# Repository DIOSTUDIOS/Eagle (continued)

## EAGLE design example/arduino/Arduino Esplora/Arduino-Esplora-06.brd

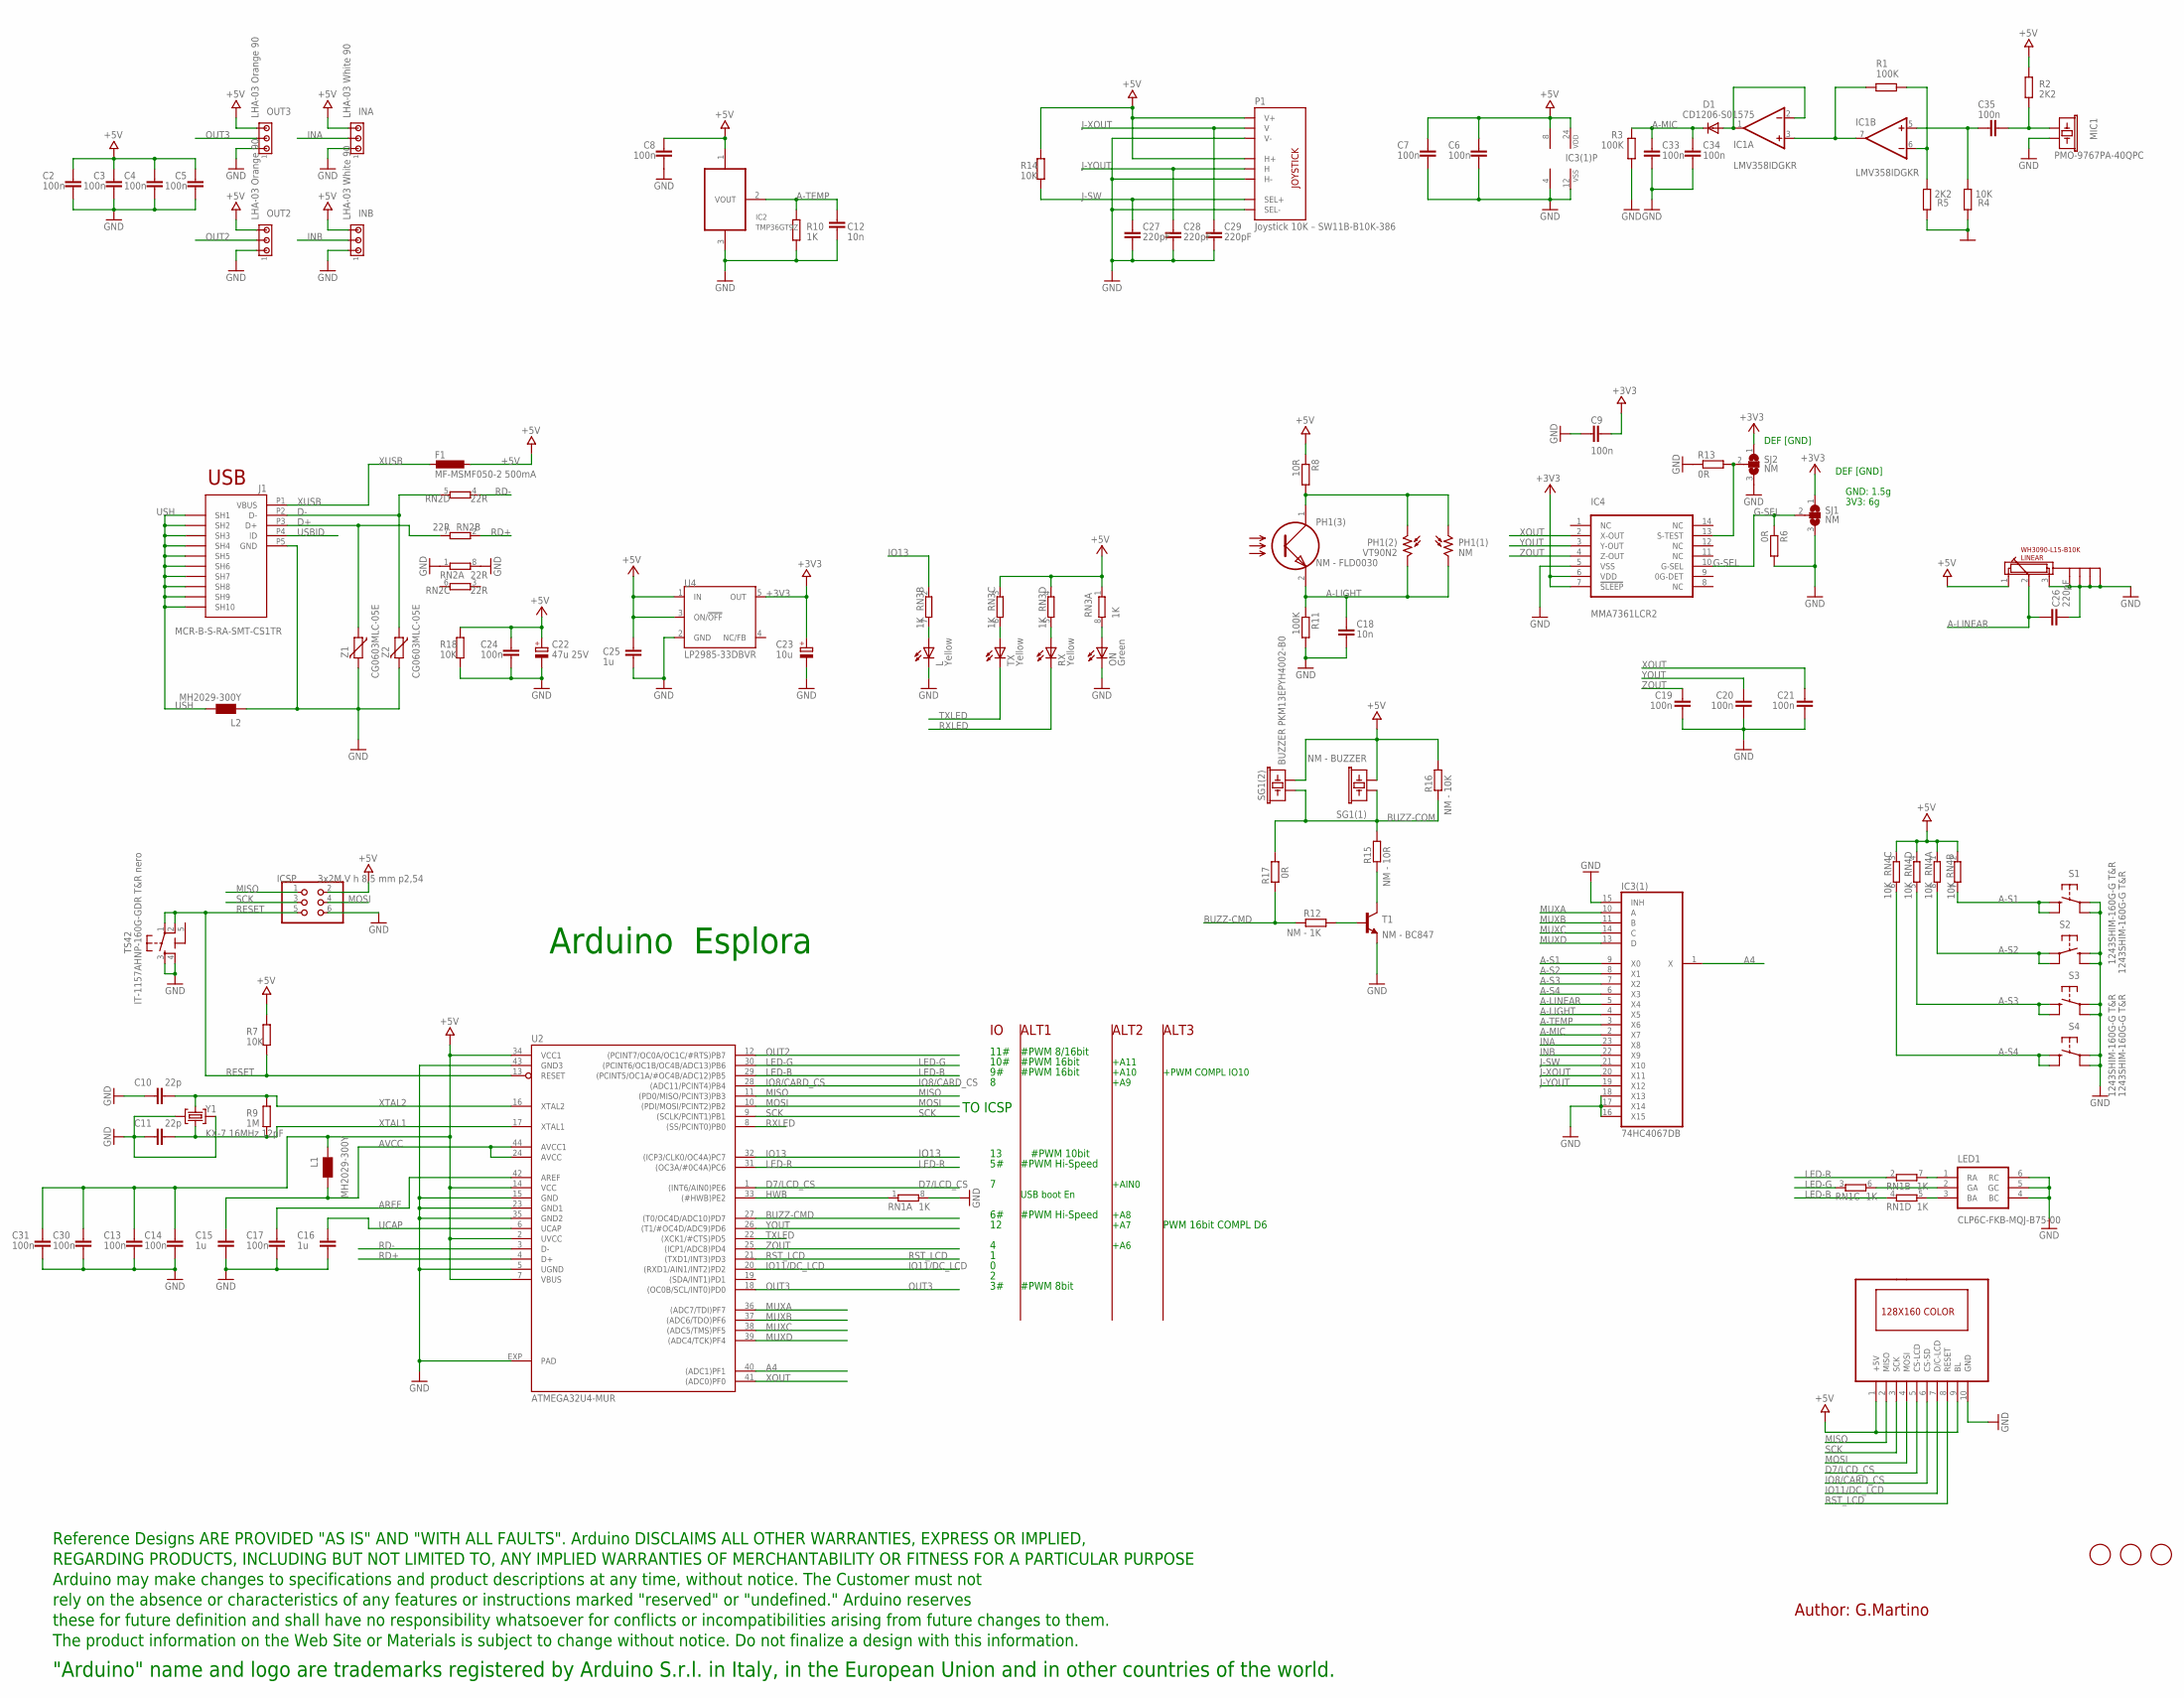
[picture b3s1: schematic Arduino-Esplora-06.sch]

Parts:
C2, C3, C4, C5, C6, C7, C8, C9, C13, C14, C17, C19, C20, C21, C24, C30, C31, C33, C34, C35: 100n; C0603-ROUND
C10, C11: 22p; C0603-ROUND
C12, C18: 10n; C0603-ROUND
C15, C16, C25: 1u; C0603-ROUND
C22: 47u 25V; PANASONIC_D
C23: 10u; SMC_B
C26, C27, C28, C29: 220pF; C0603-ROUND
D1: CD1206-S01575; MINIMELF
F1: MF-MSMF050-2 500mA; L1812
FID1, FID2, FID3: FIDUCIALMOUNT; FIDUCIA-MOUNT
IC1: LMV358IDGKR; MSOP08
IC2: TMP36GT9Z; TO92
IC3(1): 74HC4067DB; SSOP24(0.65)
IC4: MMA7361LCR2; LGA-14_3X5/0.8
ICSP: 3x2M V h 8,5 mm p2,54; 2X03
INA: LHA-03 White 90; 10X03MTA
INB: LHA-03 White 90; 10X03MTA
J1: MCR-B-S-RA-SMT-CS1TR; CON2_USB_MICRO_B_AT
L: Yellow; CHIPLED_0805
L1, L2: MH2029-300Y; 0805
LCD1: LCD1; 1.8'_LCD-LCD-TFT(128X160)
LED1: CLP6C-FKB-MQJ-B75-00; RGB-LED
LINEAR: WH3090-L15-B10K; RA3021-202
MIC1: PMO-9767PA-40QPC; MIC-9.7MM
ON: Green; CHIPLED_0805
OUT2, OUT3: LHA-03 Orange 90; 10X03MTA
P1: Joystick 10K – SW11B-B10K-386; ALP_JOYSTICK
PH1(1): NM; T0-46-A10XX
PH1(2): VT90N2; TO-8_B10
PH1(3): NM - FLD0030; FLD00030
R1, R3, R11: 100K; R0603-ROUND
R2, R5: 2K2; R0603-ROUND
R4, R7, R14, R18: 10K; R0603-ROUND
R6, R13, R17: 0R; R0603-ROUND
R8: 10R; R0603-ROUND
R9: 1M; R0603-ROUND
R10: 1K; R0603-ROUND
R12: NM - 1K; R0603-ROUND
R15: NM - 10R; R0603-ROUND
R16: NM - 10K; R0603-ROUND
RN1, RN3: 1K; CAY16
RN2: 22R; CAY16
RN4: 10K; CAY16
RX: Yellow; CHIPLED_0805
S1, S2, S3, S4: 1243SHIM-160G-G T&R; TACTILE-SMD-12MM
SG1(1): NM - BUZZER; BUZZER-12MM-NS-P5MM
SG1(2): BUZZER PKM13EPYH4002-B0; BUZZER-12MM-NS-KIT
SJ1, SJ2: NM; SJ_2
T1: NM - BC847; SOT23
TS42: IT-1157AHNP-160G-GDR T&R nero; TS42
TX: Yellow; CHIPLED_0805
U2: ATMEGA32U4-MUR; QFN44ML7X7
U4: LP2985-33DBVR; SOT23-DBV
U$19: DISCLAIMER
Y1: KX-7 16MHz 12pF; CRYSTAL-3.2-2.5
Z1, Z2: CG0603MLC-05E; CT/CN0603

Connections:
5-GND: TS42.5 (5-GND)
+3V3: C9.2, C23.+, IC4.6 (VDD), IC4.7 (!SLEEP), SJ1.1, SJ2.1, U4.5 (OUT)
+5V: C2.2, C3.2, C4.2, C5.2, C6.2, C7.2, C8.2, C13.1, C14.1, C22.+, C24.2, C25.2, C30.1, C31.1, F1.1, IC1.8 (V+), IC2.1 (+VS), IC3(1).24 (VDD), ICSP.2, INA.3, INB.3, L1.1, LCD1.1 (+5V), LCD1.9 (BL), LINEAR.1, OUT2.3, OUT3.3, P1.H1 (H+), P1.V1 (V+), R2.1, R7.1, R8.1, R14.1, R16.1, R18.1, RN3.1, RN3.3 (1), RN3.4 (1), RN4.1, RN4.2 (1), RN4.3 (1), RN4.4 (1), SG1(1).- (2), SG1(2).- (2), U2.2 (UVCC), U2.7 (VBUS), U2.14 (VCC), U2.34 (VCC1), U4.1 (IN), U4.3 (ON/!OFF)
A4: IC3(1).1 (X), U2.40 ((ADC1)PF1)
A-LIGHT: C18.2, IC3(1).4 (X5), PH1(1).2, PH1(2).2, PH1(3).2, R11.1
A-LINEAR: C26.2, IC3(1).5 (X4), LINEAR.2
A-MIC: C33.2, C34.2, D1.C, IC3(1).2 (X7), R3.1
A-S1: IC3(1).9 (X0), RN4.7 (2), S1.P$3 (3), S1.P$4 (4)
A-S2: IC3(1).8 (X1), RN4.8 (2), S2.P$1 (1), S2.P$2 (2)
A-S3: IC3(1).7 (X2), RN4.5 (2), S3.P$3 (3), S3.P$4 (4)
A-S4: IC3(1).6 (X3), RN4.6 (2), S4.P$3 (3), S4.P$4 (4)
A-TEMP: C12.2, IC2.2 (VOUT), IC3(1).3 (X6), R10.1
AREF: C17.2, U2.42 (AREF)
AVCC: C15.1, L1.2, U2.24 (AVCC), U2.44 (AVCC1)
BUZZ-CMD: R12.2, R17.2, U2.27 ((T0/OC4D/ADC10)PD7)
BUZZ-COM: R15.1, R16.2, R17.1, SG1(1).+ (1), SG1(2).+ (1)
D7/LCD_CS: LCD1.5 (CS-LCD), U2.1 ((INT6/AIN0)PE6)
D+: J1.P3 (D+), RN2.7 (2), Z1.1
D-: J1.P2 (D-), RN2.5 (2), Z2.1
G-SEL: IC4.10 (G-SEL), R6.1, SJ1.2
GND: C2.1, C3.1, C4.1, C5.1, C6.1, C7.1, C8.1, C9.1, C10.1, C11.2, C12.1, C13.2, C14.2, C15.2, C16.2, C17.1, C18.1, C19.1, C20.1, C21.1, C22.-, C23.-, C24.1, C25.1, C26.1, C27.1, C28.1, C29.1, C30.2, C31.2, C33.1, C34.1, IC1.4 (V-), IC2.3 (GND), IC3(1).12 (VSS), IC3(1).15 (INH), IC3(1).16 (X15), IC3(1).17 (X14), IC3(1).18 (X13), IC4.5 (VSS), ICSP.6, INA.1, INB.1, J1.P5 (GND), L.C, L2.1, LCD1.10 (GND), LED1.4 (BC), LED1.5 (GC), LED1.6 (RC), LINEAR.3, LINEAR.CHASSIS1 (CHASSIS-GND-1), LINEAR.CHASSIS2 (CHASSIS-GND-2), LINEAR.CHASSIS3 (CHASSIS-GND-3), LINEAR.CHASSIS4 (CHASSIS-GND-4), MIC1.2, ON.C, OUT2.1, OUT3.1, P1.B2A (SEL-), P1.H3 (H-), P1.V3 (V-), R3.2, R4.2, R5.2, R6.2, R10.2, R11.2, R13.1, R18.2, RN1.8 (2), RN2.1, RN2.8 (2), S1.P$1 (1), S1.P$2 (2), S2.P$3 (3), S2.P$4 (4), S3.P$1 (1), S3.P$2 (2), S4.P$1 (1), S4.P$2 (2), SJ1.3, SJ2.3, T1.2 (E), TS42.3, TS42.4, U2.5 (UGND), U2.15 (GND), U2.23 (GND1), U2.35 (GND2), U2.43 (GND3), U2.EXP (PAD), U4.2 (GND), Y1.2 (GND), Y1.4 (GND), Z1.2, Z2.2
HWB: RN1.1, U2.33 ((#HWB)PE2)
INA: IC3(1).23 (X8), INA.2
INB: IC3(1).22 (X9), INB.2
IO8/CARD_CS: LCD1.6 (CS-SD), U2.28 ((ADC11/PCINT4)PB4)
IO11/DC_LCD: LCD1.7 (D/C-LCD), U2.20 ((RXD1/AIN1/INT2)PD2)
IO13: RN3.2 (1), U2.32 ((ICP3/CLK0/OC4A)PC7)
J-SW: C27.2, IC3(1).21 (X10), P1.B1A (SEL+), R14.2
J-XOUT: C29.2, IC3(1).20 (X11), P1.V2 (V)
J-YOUT: C28.2, IC3(1).19 (X12), P1.H2 (H)
LED-B: RN1.4 (1), U2.29 ((PCINT5/OC1A/#OC4B/ADC12)PB5)
LED-G: RN1.3 (1), U2.30 ((PCINT6/OC1B/OC4B/ADC13)PB6)
LED-R: RN1.2 (1), U2.31 ((OC3A/#0C4A)PC6)
MISO: ICSP.1, LCD1.2 (MISO), U2.11 ((PD0/MISO/PCINT3)PB3)
MOSI: ICSP.4, LCD1.4 (MOSI), U2.10 ((PDI/MOSI/PCINT2)PB2)
MUXA: IC3(1).10 (A), U2.36 ((ADC7/TDI)PF7)
MUXB: IC3(1).11 (B), U2.37 ((ADC6/TDO)PF6)
MUXC: IC3(1).14 (C), U2.38 ((ADC5/TMS)PF5)
MUXD: IC3(1).13 (D), U2.39 ((ADC4/TCK)PF4)
unnamed: D1.A, IC1.1 (OUT), IC1.2 (-IN)
unnamed: L.A, RN3.7 (2)
unnamed: ON.A, RN3.8 (2)
unnamed: IC4.13 (S-TEST), R13.2, SJ2.2
unnamed: R15.2, T1.3 (C)
unnamed: RN3.6 (2), TX.A
unnamed: RN3.5 (2), RX.A
unnamed: LED1.1 (RA), RN1.7 (2)
unnamed: LED1.2 (GA), RN1.6 (2)
unnamed: LED1.3 (BA), RN1.5 (2)
unnamed: C35.1, MIC1.1, R2.2
unnamed: C35.2, IC1.5 (+IN), R4.1
unnamed: IC1.6 (-IN), R1.1, R5.1
unnamed: IC1.3 (+IN), IC1.7 (OUT), R1.2
unnamed: PH1(1).1, PH1(2).1, PH1(3).1, R8.2
unnamed: R12.1, T1.1 (B)
OUT2: OUT2.2, U2.12 ((PCINT7/OC0A/OC1C/#RTS)PB7)
OUT3: OUT3.2, U2.18 ((OC0B/SCL/INT0)PD0)
RD+: RN2.2 (1), U2.4 (D+)
RD-: RN2.4 (1), U2.3 (D-)
RESET: ICSP.5, R7.2, TS42.1, TS42.2, U2.13 (RESET)
RST_LCD: LCD1.8 (RESET), U2.21 ((TXD1/INT3)PD3)
RXLED: RX.C, U2.8 ((SS/PCINT0)PB0)
SCK: ICSP.3, LCD1.3 (SCK), U2.9 ((SCLK/PCINT1)PB1)
TXLED: TX.C, U2.22 ((XCK1/#CTS)PD5)
UCAP: C16.1, U2.6 (UCAP)
USBID: J1.P4 (ID)
USH: J1.P$1 (SH7), J1.P$2 (SH8), J1.P$3 (SH9), J1.P$4 (SH10), J1.P$5 (SH7), J1.P$6 (SH8), J1.P$7 (SH9), J1.P$8 (SH10), J1.S1 (SH1), J1.S2 (SH2), J1.S3 (SH3), J1.S4 (SH4), J1.S5 (SH5), J1.S6 (SH6), L2.2
XOUT: C21.2, IC4.2 (X-OUT), U2.41 ((ADC0)PF0)
XTAL1: C11.1, R9.1, U2.17 (XTAL1), Y1.1 (C1)
XTAL2: C10.2, R9.2, U2.16 (XTAL2), Y1.3 (C2)
XUSB: F1.2, J1.P1 (VBUS)
YOUT: C20.2, IC4.3 (Y-OUT), U2.26 ((T1/#OC4D/ADC9)PD6)
ZOUT: C19.2, IC4.4 (Z-OUT), U2.25 ((ICP1/ADC8)PD4)

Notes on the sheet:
Arduino Esplora
USB boot En
USB
TO ICSP
10#
11#
#PWM 8bit
#PWM Hi-Speed
#PWM 8/16bit
#PWM 16bit
PWM 16bit COMPL D6
#PWM 10bit
+A6
+A7
+A11
+A10
+A8
+A9
+PWM COMPL IO10
+AIN0
ALT1
ALT2
ALT3
GND: 1.5g
3V3: 6g
DEF [GND]
Author: G.Martino

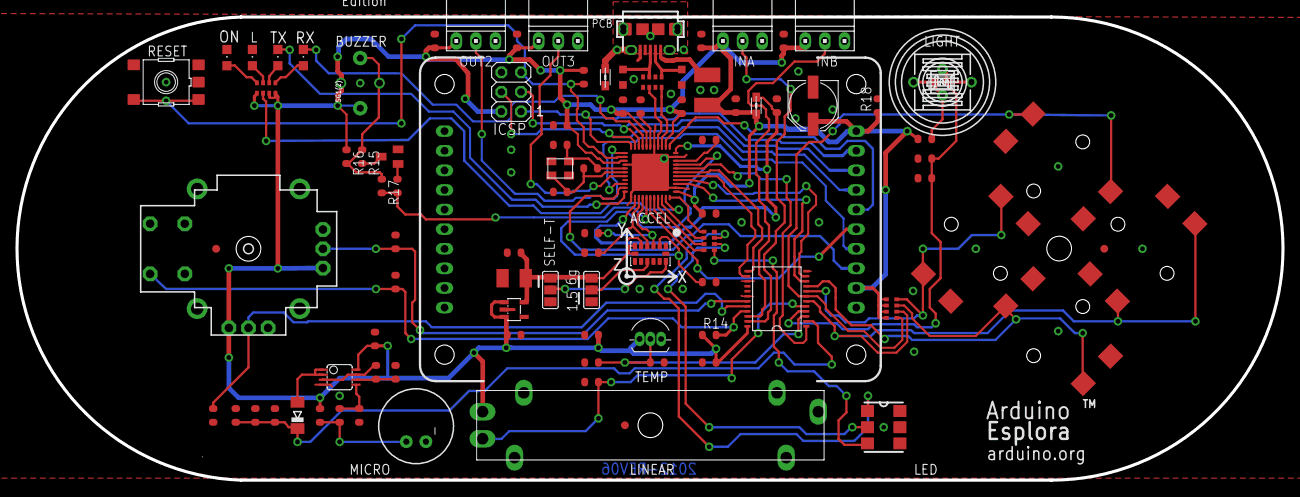
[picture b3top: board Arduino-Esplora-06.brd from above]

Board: 2 copper layers, 164.0 x 60.0 mm, 100 parts (0 on the bottom side), 71 nets.

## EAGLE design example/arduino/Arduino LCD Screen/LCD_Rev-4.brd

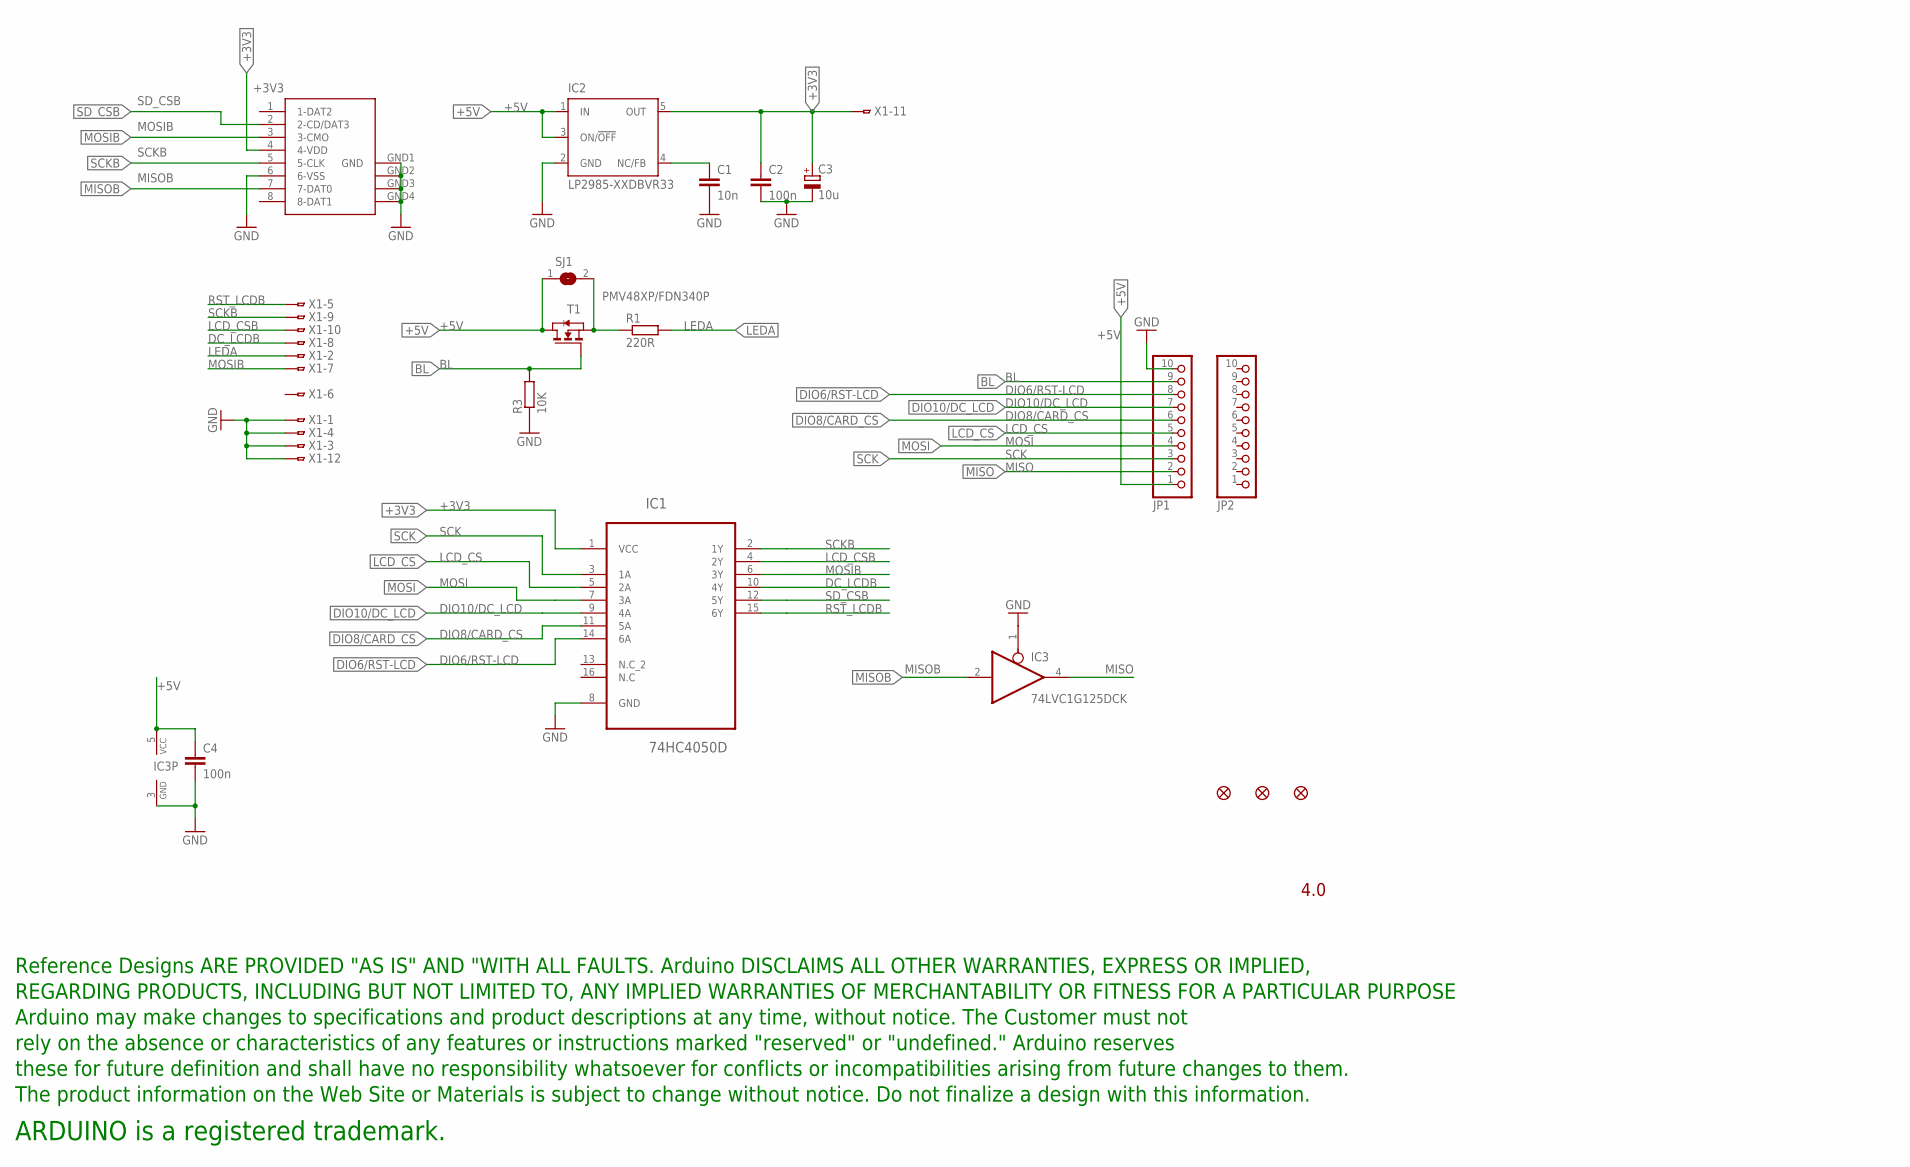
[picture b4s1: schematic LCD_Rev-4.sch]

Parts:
C1: 10n; C0603-ROUND
C2, C4: 100n; C0603-ROUND
C3: 10u; SMC_B
IC1: 74HC4050D; SOIC127P600X175-16N
IC2: LP2985-XXDBVR33; SOT23-DBV
IC3: 74LVC1G125DCK; SC70-5
JP1, JP2: PINHD-1X10TH; 1X10-TH
R1: 220R; R0603-ROUND
R3: 10K; R0603-ROUND
SJ1: SJL
T1: PMV48XP/FDN340P; SOT-23
U1: SDCARD-15TW-8821
U$1, U$3, U$4: FIDUCIAL-LITTLE1X2; FIDUCIAL-1X2
U$2: DISCLAIMER
X1: FH12-12S-0.8SH

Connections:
+3V3: C2.1, C3.+, IC1.1 (VCC), IC2.5 (OUT), U1.4 (4-VDD), X1.11
+5V: C4.1, IC2.1 (IN), IC2.3 (ON/!OFF), IC3.5 (VCC), JP1.1, SJ1.1, T1.1 (D)
BL: JP1.9, R3.2, T1.3 (G)
DC_LCDB: IC1.10 (4Y), X1.8
DIO6/RST-LCD: IC1.14 (6A), JP1.8
DIO8/CARD_CS: IC1.11 (5A), JP1.6
DIO10/DC_LCD: IC1.9 (4A), JP1.7
GND: C1.2, C2.2, C3.-, C4.2, IC1.8 (GND), IC2.2 (GND), IC3.1 (OE), IC3.3 (GND), JP1.10, R3.1, U1.6 (6-VSS), U1.GND1 (GND), U1.GND2 (GND1), U1.GND3 (GND2), U1.GND4 (GND3), X1.1, X1.3, X1.4, X1.12
LCD_CS: IC1.5 (2A), JP1.5
LCD_CSB: IC1.4 (2Y), X1.10
LEDA: R1.2, X1.2
MISO: IC3.4 (O), JP1.2
MISOB: IC3.2 (I), U1.7 (7-DAT0)
MOSI: IC1.7 (3A), JP1.4
MOSIB: IC1.6 (3Y), U1.3 (3-CMO), X1.7
unnamed: C1.1, IC2.4 (NC/FB)
unnamed: R1.1, SJ1.2, T1.2 (S)
RST_LCDB: IC1.15 (6Y), X1.5
SCK: IC1.3 (1A), JP1.3
SCKB: IC1.2 (1Y), U1.5 (5-CLK), X1.9
SD_CSB: IC1.12 (5Y), U1.2 (2-CD/DAT3)

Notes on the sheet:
4.0

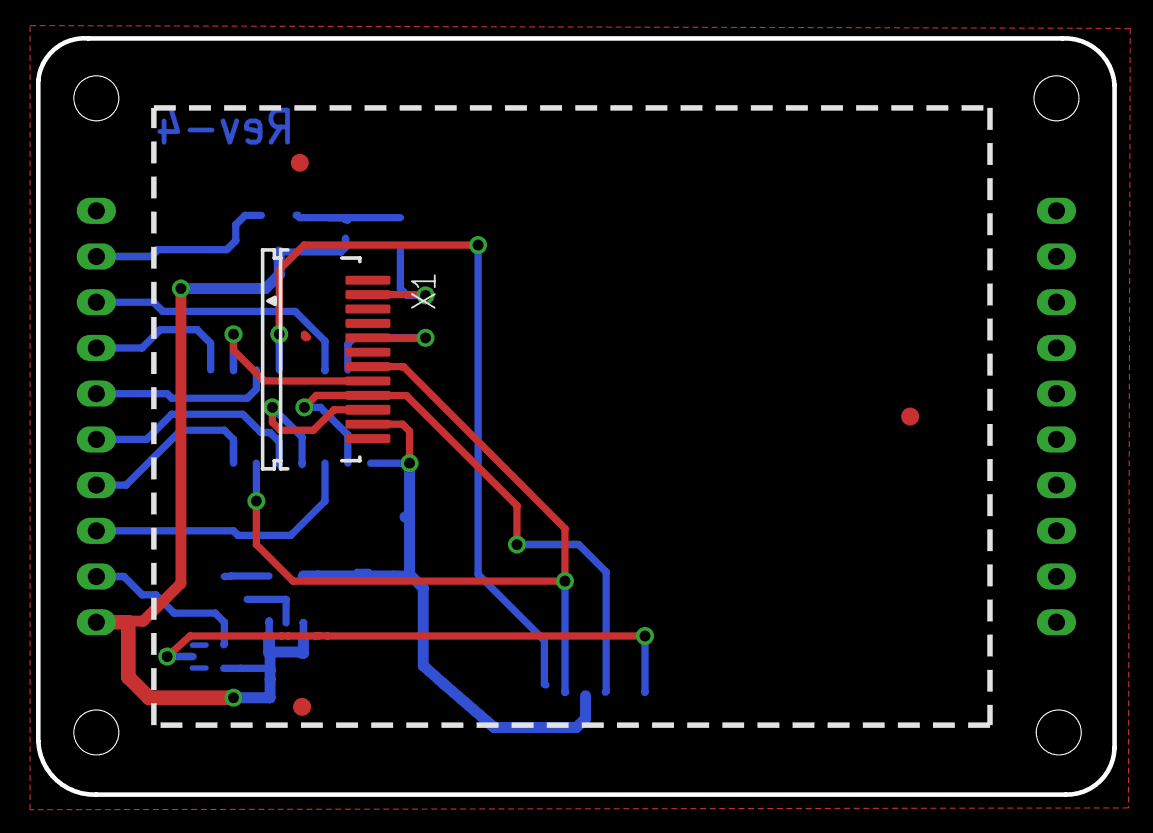
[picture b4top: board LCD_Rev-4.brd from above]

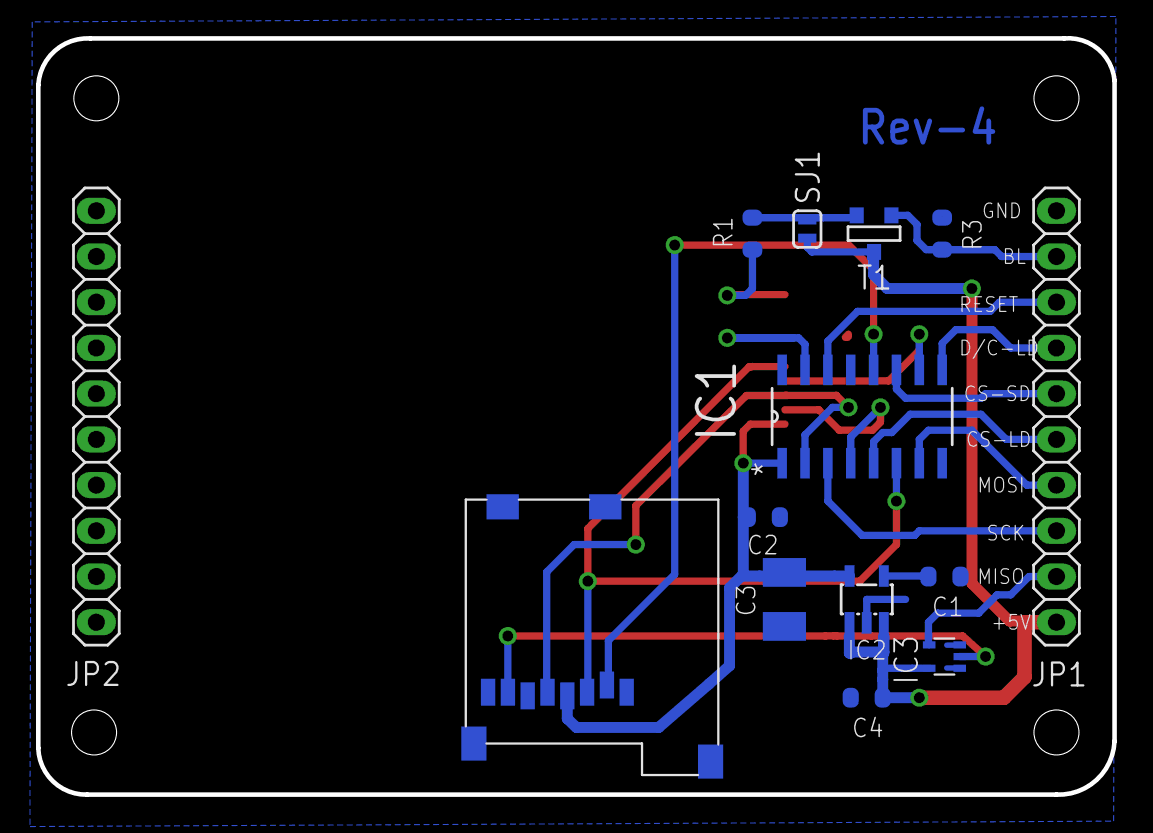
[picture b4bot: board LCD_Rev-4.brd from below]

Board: 2 copper layers, 59.8 x 42.0 mm, 19 parts (14 on the bottom side), 21 nets.

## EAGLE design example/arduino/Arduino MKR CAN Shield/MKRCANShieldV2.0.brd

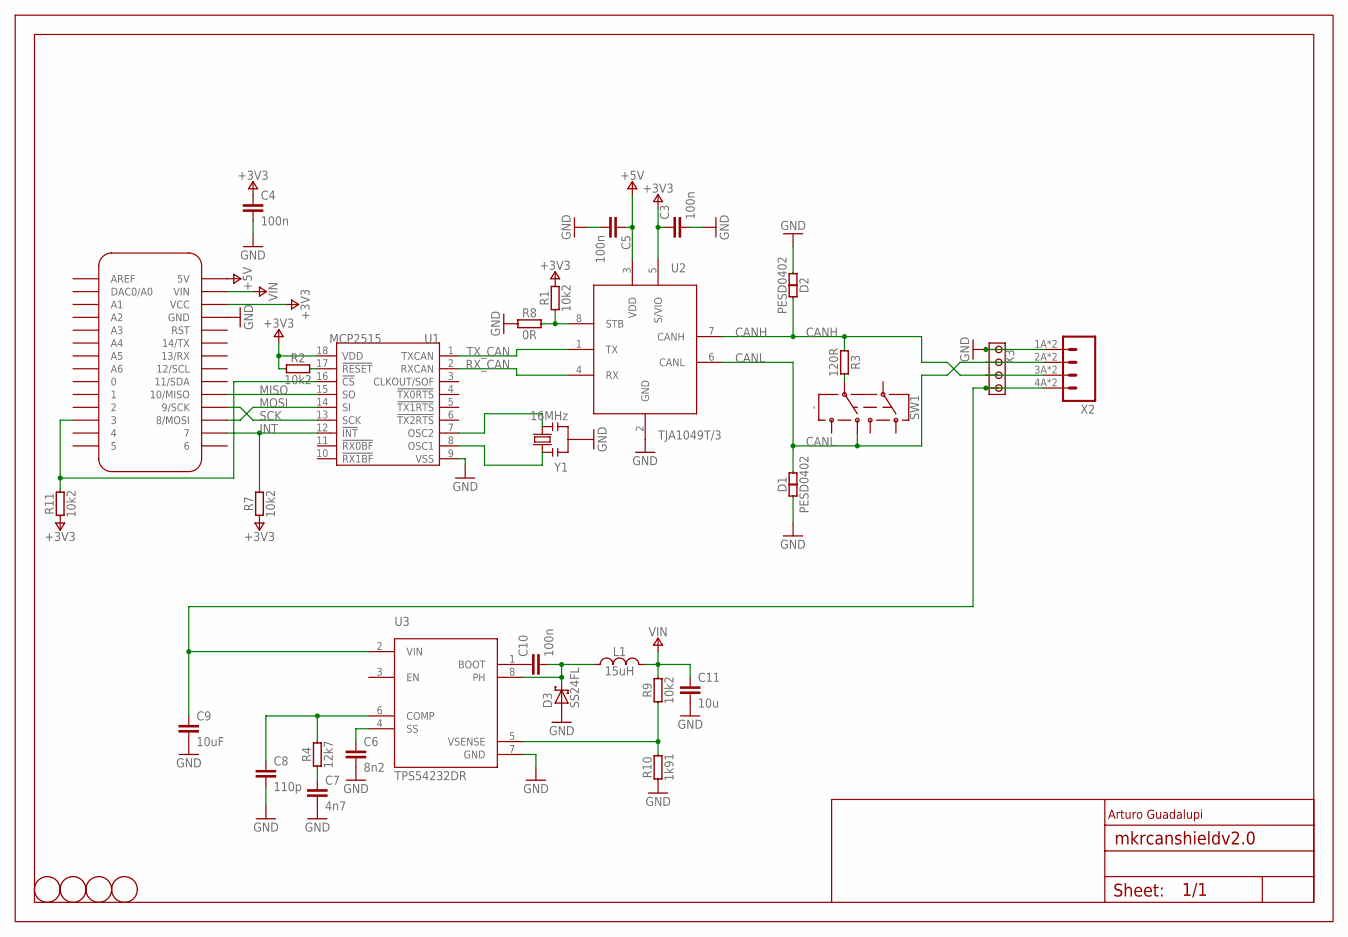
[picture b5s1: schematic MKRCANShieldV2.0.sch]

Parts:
C3, C4, C5, C10: 100n; 0402-1005X55N
C6: 8n2; 0402-1005X55N
C7: 4n7; 0402-1005X55N
C8: 110p; 0402-1005X55N
C9: 10uF; C1206
C11: 10u; 0603-1608X90N
D1, D2: PESD0402; 0402-1005X55N
D3: SS24FL; SOD123F
FRAME1: DNP; FRAME
L1: 15uH; SRN6045
MKR1: -; MKRBOARD-NH
R1, R2, R7, R9, R11: 10k2; 0402-1005X55N
R3: 120R; 0402-1005X55N
R4: 12k7; 0402-1005X55N
R8: 0R; 0402-1005X55N
R10: 1k91; 0402-1005X55N
SW1: -; CL-SB-22A
U1: MCP2515; SOIC18
U2: TJA1049T/3; SO08
U3: TPS54232DR; SO08
U$1, U$4, U$6, U$13: DNP; FD-1-1.5
X2: DNP; SPTAF1/4-3.5-IL
X3: -; MODULINO-4
Y1: 16MHz; RESONATOR

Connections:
+3V3: C3.1, C4.1, MKR1.VCC, R1.2, R2.2, R7.2, R11.2, U1.18 (VDD), U2.5 (S/VIO)
+5V: C5.1, MKR1.5V, U2.3 (VDD)
CANH: D2.2, R3.1, U2.7 (CANH), X2.3A (3), X2.3B (3), X3.3
CANL: D1.2, SW1.P$4 (4), U2.6 (CANL), X2.2A (2), X2.2B (2), X3.2
GND: C3.2, C4.2, C5.2, C6.2, C7.2, C8.2, C9.2, C11.2, D1.1, D2.1, D3.A, MKR1.GND, R8.1, R10.1, U1.9 (VSS), U2.2 (GND), U3.7 (GND), X2.1A (1), X2.1B (1), X3.1, Y1.2
INT: MKR1.7, R7.1, U1.12 (!INT)
MISO: MKR1.10 (10/MISO), U1.15 (SO)
MOSI: MKR1.8 (8/MOSI), U1.14 (SI)
unnamed: R3.2, SW1.P$5 (5)
unnamed: C7.1, R4.1
unnamed: R1.1, R8.2, U2.8 (STB)
unnamed: C8.1, R4.2, U3.6 (COMP)
unnamed: C6.1, U3.4 (SS)
unnamed: C9.1, U3.2 (VIN), X2.4A (4), X2.4B (4), X3.4
unnamed: C10.1, U3.1 (BOOT)
unnamed: C10.2, D3.C, L1.1, U3.8 (PH)
unnamed: R9.1, R10.2, U3.5 (VSENSE)
unnamed: MKR1.3, R11.1, U1.16 (!CS)
unnamed: U1.7 (OSC2), Y1.3
unnamed: U1.8 (OSC1), Y1.1
RST_N: R2.1, U1.17 (!RESET)
RX_CAN: U1.2 (RXCAN), U2.4 (RX)
SCK: MKR1.9 (9/SCK), U1.13 (SCK)
TX_CAN: U1.1 (TXCAN), U2.1 (TX)
VIN: C11.1, L1.2, MKR1.VIN, R9.2

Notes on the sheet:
Arturo Guadalupi

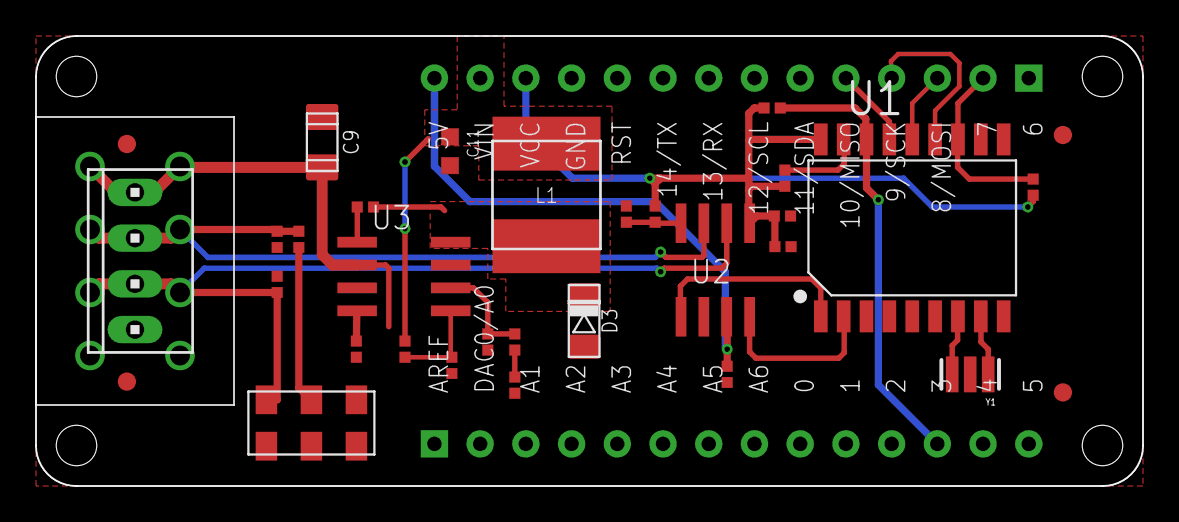
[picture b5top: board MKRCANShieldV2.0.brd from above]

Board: 2 copper layers, 61.5 x 25.0 mm, 35 parts (0 on the bottom side), 25 nets.

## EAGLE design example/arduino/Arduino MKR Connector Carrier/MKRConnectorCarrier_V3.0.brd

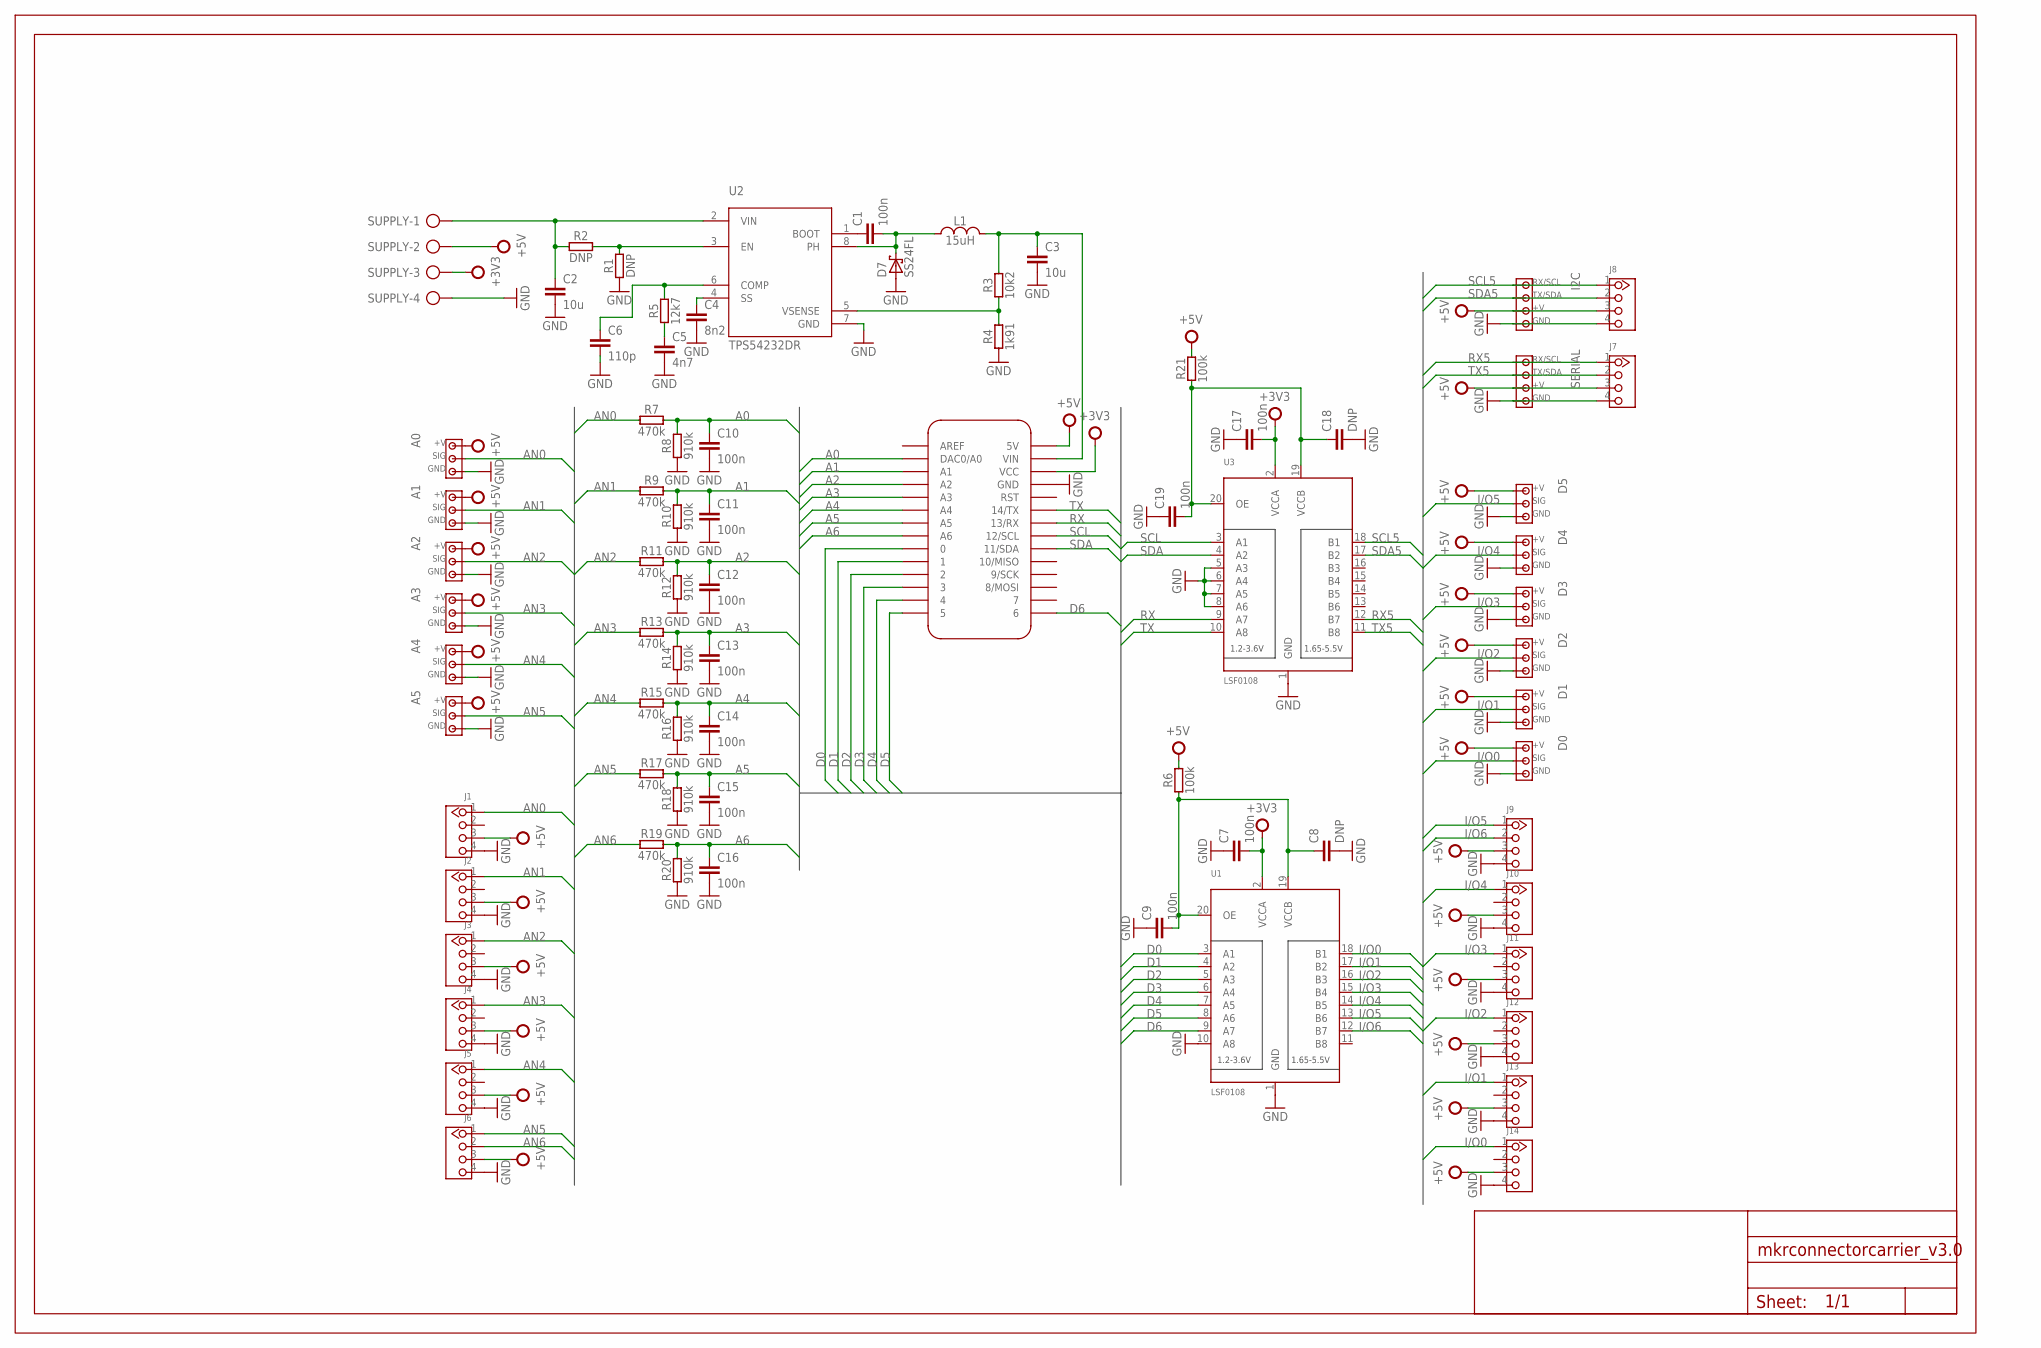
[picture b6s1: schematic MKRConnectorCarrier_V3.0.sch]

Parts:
A0, A1, A2, A3, A4, A5: DNP; MODULINO-3SM
B1: DNP; MKRBOARD-NOOUTLINE
C1, C7, C9, C10, C11, C12, C13, C14, C15, C16, C17, C19: 100n; 0402-1005X55N
C2, C3: 10u; 0603-1608X90N
C4: 8n2; 0402-1005X55N
C5: 4n7; 0402-1005X55N
C6: 110p; 0402-1005X55N
C8, C18: DNP; 0402-1005X55N
D0, D1, D2, D3, D4, D5: DNP; MODULINO-3SM
D7: SS24FL; SOD123F
FRAME1: DNP; FRAME
I2C: DNP; MODULINO-4SM
J1, J2, J3, J4, J5, J6, J7, J8, J9, J10, J11, J12, J13, J14: -; HW4-2.0
L1: 15uH; SRN6045
R1, R2: DNP; 0402-1005X55N
R3: 10k2; 0402-1005X55N
R4: 1k91; 0402-1005X55N
R5: 12k7; 0402-1005X55N
R6, R21: 100k; 0402-1005X55N
R7, R9, R11, R13, R15, R17, R19: 470k; 0402-1005X55N
R8, R10, R12, R14, R16, R18, R20: 910k; 0402-1005X55N
SERIAL: DNP; MODULINO-4SM
SUPPLY: -; AK300/4
U1, U3: LSF0108; TSSOP20
U2: TPS54232DR; SO08

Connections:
+3V3: B1.VCC, C7.2, C17.2, SUPPLY.3, U1.2 (VCCA), U3.2 (VCCA)
+5V: A0.1, A1.1, A2.1, A3.1, A4.1, A5.1, B1.5V, D0.1, D1.1, D2.1, D3.1, D4.1, D5.1, I2C.3, J1.3, J2.3, J3.3, J4.3, J5.3, J6.3, J7.3, J8.3, J9.3, J10.3, J11.3, J12.3, J13.3, J14.3, R6.2, R21.2, SERIAL.3, SUPPLY.2
A0: B1.A0 (DAC0/A0), C10.1, R7.2, R8.2
A1: B1.A1, C11.1, R9.2, R10.2
A2: B1.A2, C12.1, R11.2, R12.2
A3: B1.A3, C13.1, R13.2, R14.2
A4: B1.A4, C14.1, R15.2, R16.2
A5: B1.A5, C15.1, R17.2, R18.2
A6: B1.A6, C16.1, R19.2, R20.2
AN0: A0.2, J1.1, R7.1
AN1: A1.2, J2.1, R9.1
AN2: A2.2, J3.1, R11.1
AN3: A3.2, J4.1, R13.1
AN4: A4.2, J5.1, R15.1
AN5: A5.2, J6.1, R17.1
AN6: J6.2, R19.1
D0: B1.0, U1.3 (A1)
D1: B1.1, U1.4 (A2)
D2: B1.2, U1.5 (A3)
D3: B1.3, U1.6 (A4)
D4: B1.4, U1.7 (A5)
D5: B1.5, U1.8 (A6)
D6: B1.6, U1.9 (A7)
GND: A0.3, A1.3, A2.3, A3.3, A4.3, A5.3, B1.GND, C2.2, C3.2, C4.2, C5.2, C6.2, C7.1, C8.2, C9.1, C10.2, C11.2, C12.2, C13.2, C14.2, C15.2, C16.2, C17.1, C18.2, C19.1, D0.3, D1.3, D2.3, D3.3, D4.3, D5.3, D7.A, I2C.4, J1.4, J2.4, J3.4, J4.4, J5.4, J6.4, J7.4, J8.4, J9.4, J10.4, J11.4, J12.4, J13.4, J14.4, R1.1, R4.1, R8.1, R10.1, R12.1, R14.1, R16.1, R18.1, R20.1, SERIAL.4, SUPPLY.4, U1.1 (GND), U1.10 (A8), U2.7 (GND), U3.1 (GND), U3.5 (A3), U3.6 (A4), U3.7 (A5), U3.8 (A6)
I/O0: D0.2, J14.1, U1.18 (B1)
I/O1: D1.2, J13.1, U1.17 (B2)
I/O2: D2.2, J12.1, U1.16 (B3)
I/O3: D3.2, J11.1, U1.15 (B4)
I/O4: D4.2, J10.1, U1.14 (B5)
I/O5: D5.2, J9.1, U1.13 (B6)
I/O6: J9.2, U1.12 (B7)
unnamed: C2.1, R2.1, SUPPLY.1, U2.2 (VIN)
unnamed: R1.2, R2.2, U2.3 (EN)
unnamed: C1.1, U2.1 (BOOT)
unnamed: C1.2, D7.C, L1.1, U2.8 (PH)
unnamed: C4.1, U2.4 (SS)
unnamed: R3.1, R4.2, U2.5 (VSENSE)
unnamed: C6.1, R5.2, U2.6 (COMP)
unnamed: C5.1, R5.1
unnamed: C8.1, C9.2, R6.1, U1.19 (VCCB), U1.20 (OE)
unnamed: C18.1, C19.2, R21.1, U3.19 (VCCB), U3.20 (OE)
RX: B1.13 (13/RX), U3.9 (A7)
RX5: J7.1, SERIAL.1, U3.12 (B7)
SCL: B1.12 (12/SCL), U3.3 (A1)
SCL5: I2C.1, J8.1, U3.18 (B1)
SDA: B1.11 (11/SDA), U3.4 (A2)
SDA5: I2C.2, J8.2, U3.17 (B2)
TX: B1.14 (14/TX), U3.10 (A8)
TX5: J7.2, SERIAL.2, U3.11 (B8)
VIN: B1.VIN, C3.1, L1.2, R3.2

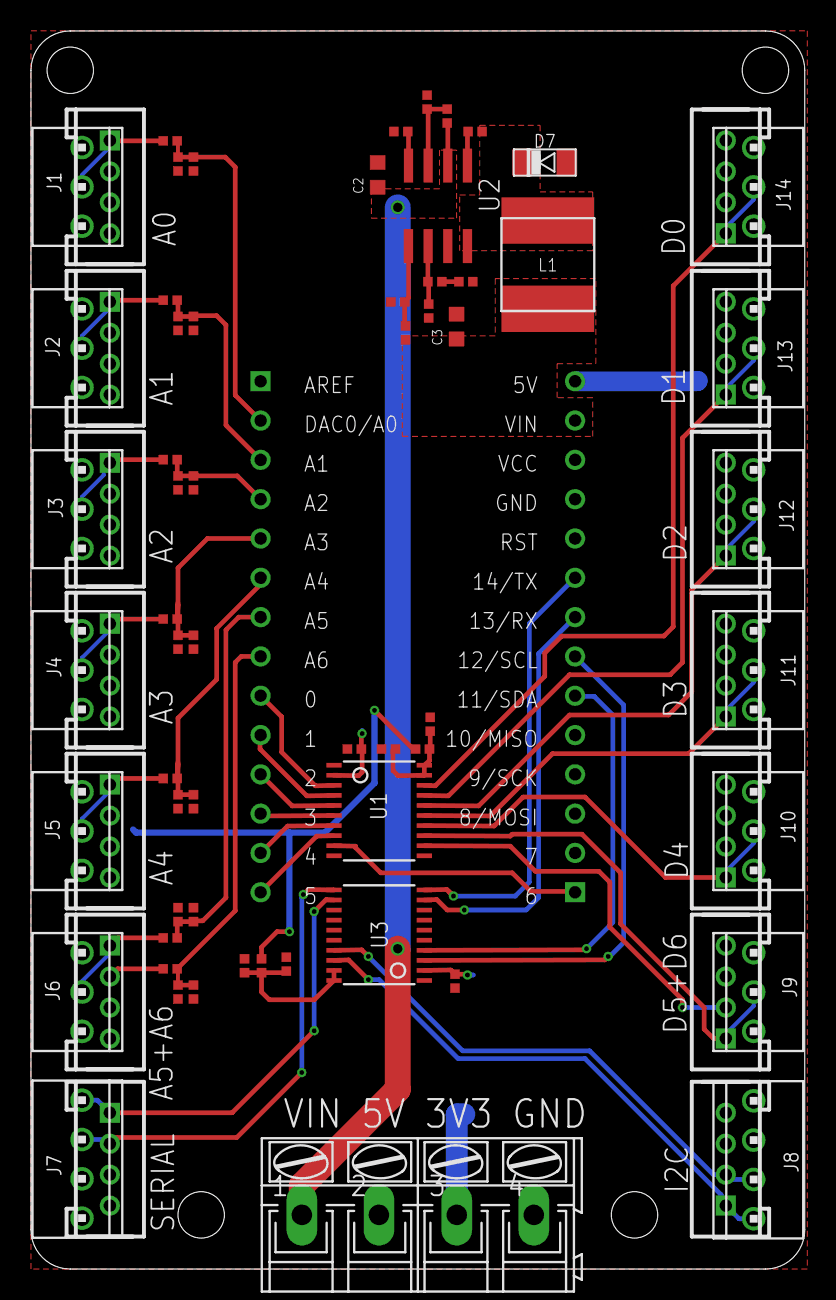
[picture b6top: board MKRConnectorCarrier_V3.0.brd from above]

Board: 2 copper layers, 50.0 x 80.0 mm, 76 parts (0 on the bottom side), 50 nets.
